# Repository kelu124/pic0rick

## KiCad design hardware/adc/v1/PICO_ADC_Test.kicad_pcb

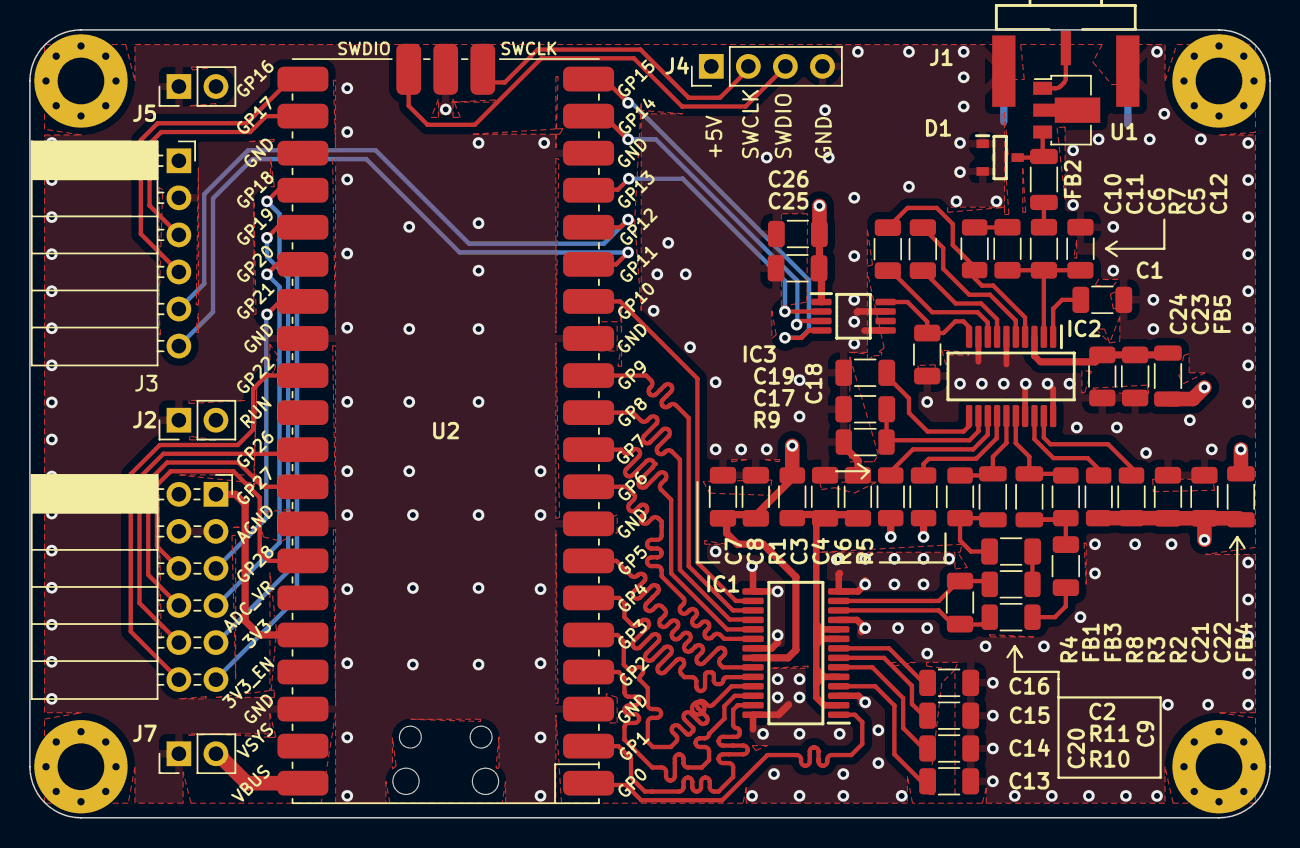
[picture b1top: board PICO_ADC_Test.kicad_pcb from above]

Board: 4 copper layers, 85.0 x 54.0 mm, 55 parts (0 on the bottom side), 63 nets.

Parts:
C1, C2, C4, C5, C8, C9, C10, C11, C13, C14, C15, C16, C17, C19, C22, C24, C26: 100nF; C_1206_3216Metric
C3, C7: 4.7uF; C_1206_3216Metric
C6: 18nF; C_1206_3216Metric
C12: 22pF; C_1206_3216Metric
C18, C21, C23: 1nF; C_1206_3216Metric
C20: 50pF; C_1206_3216Metric
C25: 10uF; C_1206_3216Metric
D1: BAV99-7-F; SOT95P240X120-3N
FB1, FB2, FB3, FB4, FB5: ILHB1206ER750V; L_1206_3216Metric
IC1: ADC10065CIMT_NOPB; SOP65P640X120-28N
IC2: AD8331ARQZ; SOP64P600X175-20N
IC3: MCP4812-E_MS; MCP4812-EMS
J1: AMPHENOL_132357-11
J2, J5, J7: 22-23-2021; PinHeader_1x02_P2.54mm_Vertical
J3: 61300611121; PinSocket_1x06_P2.54mm_Horizontal
J4: Conn_01x04; PinHeader_1x04_P2.54mm_Vertical
J6: 90122-0126; PinSocket_2x06_P2.54mm_Horizontal
R1, R10, R11: 18R; R_1206_3216Metric
R2, R3, R5, R6: 10K; R_1206_3216Metric
R4, R8: 100R; R_1206_3216Metric
R7: 280R; R_1206_3216Metric
R9: 12K; R_1206_3216Metric
U1: MD0100N8-G; SOT-89-3
U2: Pico; RPi_Pico_SMD

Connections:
5VLNA: C23.1, C24.1, FB5.2, IC2.3 (VPSL)
5VVGA: C21.1, C22.1, FB4.1, R2.1, R3.1, R5.1, R6.1
+3.3V: C7.1, C8.1, C25.1, C26.1, IC1.22 (VDDIO), IC3.1 (VDD), J3.1, J6.1, J6.2, R1.1, U2.36 (3V3)
+5V: FB4.2, FB5.1, J2.2, J4.1, J5.2, J7.2, U2.40 (VBUS)
ADC_CLK: IC1.1 (CLK), U2.1 (GPIO0)
CS: IC3.2 (~CS), U2.17 (GPIO13)
D0: IC1.27 (D0), U2.2 (GPIO1)
D1: IC1.26 (D1), U2.4 (GPIO2)
D2: IC1.25 (D2), U2.5 (GPIO3)
D3: IC1.24 (D3), U2.6 (GPIO4)
D4: IC1.23 (D4), U2.7 (GPIO5)
D5: IC1.20 (D5), U2.9 (GPIO6)
D6: IC1.19 (D6), U2.10 (GPIO7)
D7: IC1.18 (D7), U2.11 (GPIO8)
D8: IC1.17 (D8), U2.12 (GPIO9)
D9: IC1.16 (D9), U2.14 (GPIO10)
DAC_G: C18.1, IC2.10 (GAIN), IC3.8 (VOUTA)
GND: C1.1, C3.2, C4.2, C7.2, C8.2, C12.2, C13.2, C14.2, C15.2, C16.2, C17.2, C18.2, C19.2, C21.2, C22.2, C23.2, C24.2, C25.2, C26.2, D1.1, D1.2, IC1.3 (VSSA_1), IC1.11 (VSSA_2), IC1.14 (VSSA_3), IC1.15 (DF), IC1.21 (VSSIO), IC1.28 (STBY), IC2.6 (COML), IC2.9 (MODE), IC2.17 (COMM_1), IC2.20 (COMM_2), IC3.5 (~LDAC), IC3.7 (VSS), J1.2, J2.1, J3.2, J4.4, J5.1, J6.3, J6.4, J7.1, R9.2, U2.3 (GND), U2.8 (GND), U2.13 (GND), U2.18 (GND), U2.23 (GND), U2.28 (GND), U2.33 (AGND), U2.38 (GND), U2.42 (GND)
GPIO11: J3.6, U2.15 (GPIO11)
GPIO12: J3.5, U2.16 (GPIO12)
GPIO16: J3.4, U2.21 (GPIO16)
GPIO17: J3.3, U2.22 (GPIO17)
GPIO18: J6.11, U2.24 (GPIO18)
GPIO19: J6.9, U2.25 (GPIO19)
GPIO20: J6.7, U2.26 (GPIO20)
GPIO21: J6.5, U2.27 (GPIO21)
GPIO22: J6.12, U2.29 (GPIO22)
GPIO26: J6.10, U2.31 (GPIO26_ADC0)
GPIO27: J6.8, U2.32 (GPIO27_ADC1)
GPIO28: J6.6, U2.34 (GPIO28_ADC2)
MOSI: IC3.4 (SDI), U2.20 (GPIO15)
unnamed: C2.1, FB1.2, R4.2
unnamed: C5.1, FB2.2
unnamed: C6.2, R7.1
unnamed: C9.1, FB3.2, R8.2
unnamed: C3.1, C4.1, IC1.2 (VDDA_1), IC1.5 (IRS), IC1.9 (VDDA_2), IC1.10 (VDDA_3), R1.2
unnamed: C13.1, IC1.4 (VCOM)
unnamed: C20.2, IC1.13 (VIN+), R11.1
unnamed: C20.1, IC1.12 (VIN-), R10.1
unnamed: C14.1, IC1.6 (VREF)
unnamed: C16.1, IC1.8 (VREFB)
unnamed: C15.1, IC1.7 (VREFT)
unnamed: IC2.19 (ENBL), R2.2
unnamed: IC2.18 (ENBV), R3.2
unnamed: IC2.13 (HILO), R6.2
unnamed: C5.2, C6.1, C12.1, IC2.2 (INH)
unnamed: C1.2, IC2.1 (LMD)
unnamed: C10.1, IC2.4 (LON), R7.2
unnamed: C11.1, IC2.5 (LOP)
unnamed: C17.1, IC2.12 (RCLMP), R9.1
unnamed: C19.1, IC2.11 (VCM)
unnamed: C10.2, IC2.8 (VIN)
unnamed: C11.2, IC2.7 (VIP)
unnamed: IC2.14 (VPOS), R5.2
unnamed: J1.1, U1.1 (A)
unnamed: D1.3, FB2.1, U1.3 (B)
SCLK: IC3.3 (SCK), U2.19 (GPIO14)
SWCLK: J4.2, U2.41 (SWCLK)
SWDIO: J4.3, U2.43 (SWDIO)
TO_ADC_H: C2.2, R11.2
TO_ADC_L: C9.2, R10.2
VOH: FB1.1, IC2.15 (VOH), R4.1
VOL: FB3.1, IC2.16 (VOL), R8.1

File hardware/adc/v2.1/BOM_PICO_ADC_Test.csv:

"Reference","Value","Footprint","MPN","Manufacturer","Size","Qty"
"C1,C2,C4,C5,C8,C9,C10,C11,C13,C14,C15,C16,C17,C19,C22,C24,C26","100nF","Capacitor_SMD:C_1206_3216Metric","VJ1206Y104KXQCW1BC","","1206","17"
"C3,C7","4.7uF","Capacitor_SMD:C_1206_3216Metric","1206ZD475KAT4A","","1206","2"
"C6","18nF","Capacitor_SMD:C_1206_3216Metric","VJ1206Y183KXAAC","","1206","1"
"C12","22pF","Capacitor_SMD:C_1206_3216Metric","VJ1206A220JXQPW1BC","","1206","1"
"C18,C21,C23","1nF","Capacitor_SMD:C_1206_3216Metric","GRM31C5C3A102JWA3L","","1206","3"
"C20","50pF","Capacitor_SMD:C_1206_3216Metric","12062A500KAT2A","KYOCERA AVX","1206","1"
"C25","10uF","Capacitor_SMD:C_1206_3216Metric","KAF31GR71C106KU","KYOCERA AVX","1206","1"
"D1","BAV99-7-F","PICO_ADC_Test:SOT95P240X120-3N","BAV99-7-F","","SOT23","1"
"FB1,FB2,FB3,FB4,FB5","ILHB1206ER750V","Inductor_SMD:L_1206_3216Metric","BLM21BB750SN1D","","1206","5"
"IC1","ADC10065CIMT_NOPB","PICO_ADC_Test:SOP65P640X120-28N","ADC10065CIMT/NOPB","","","1"
"IC2","AD8331ARQZ","PICO_ADC_Test:SOP64P600X175-20N","584-AD8331ARQZ","","","1"
"IC3","MCP4812-E_MS","PICO_ADC_Test:MCP4812-EMS","579-MCP4812-E/MS","","","1"
"J1","AMPHENOL_132357-11","PICO_ADC_Test:AMPHENOL_132357-11","142-0701-801","","","1"
"J2,J5,J7","SSQ-101-02-L-Q-RA","Connector_PinHeader_2.54mm:PinHeader_1x02_P2.54mm_Vertical","SSQ-101-02-L-Q-RA","","","3"
"J3","61300611121","Connector_PinSocket_2.54mm:PinSocket_1x06_P2.54mm_Horizontal","613012243121","","","1"
"J4","61300411121","Connector_PinHeader_2.54mm:PinHeader_1x04_P2.54mm_Vertical","61300411121","","","1"
"J6","90122-0126","Connector_PinSocket_2.54mm:PinSocket_2x06_P2.54mm_Horizontal","613012243121","","","1"
"R1,R10,R11","18R","Resistor_SMD:R_1206_3216Metric","WSL1206R1800FEA","","1206","3"
"R2,R3,R5,R6","10K","Resistor_SMD:R_1206_3216Metric","1206W4F1002T5E","","1206","4"
"R4,R8","100R","Resistor_SMD:R_1206_3216Metric","560112132023","","1206","2"
"R7","280R","Resistor_SMD:R_1206_3216Metric","CR1206-FX-2800ELF","Bourns","1206","1"
"R9","12K","Resistor_SMD:R_1206_3216Metric","CR1206-FX-1202ELF","Bourns","1206","1"
"U1","MD0100N8-G","Package_TO_SOT_SMD:SOT-89-3","MD0100N8-G","","","1"
"U2","Pico","PICO_ADC_Test:RPi_Pico_SMD","Pico","","","1"

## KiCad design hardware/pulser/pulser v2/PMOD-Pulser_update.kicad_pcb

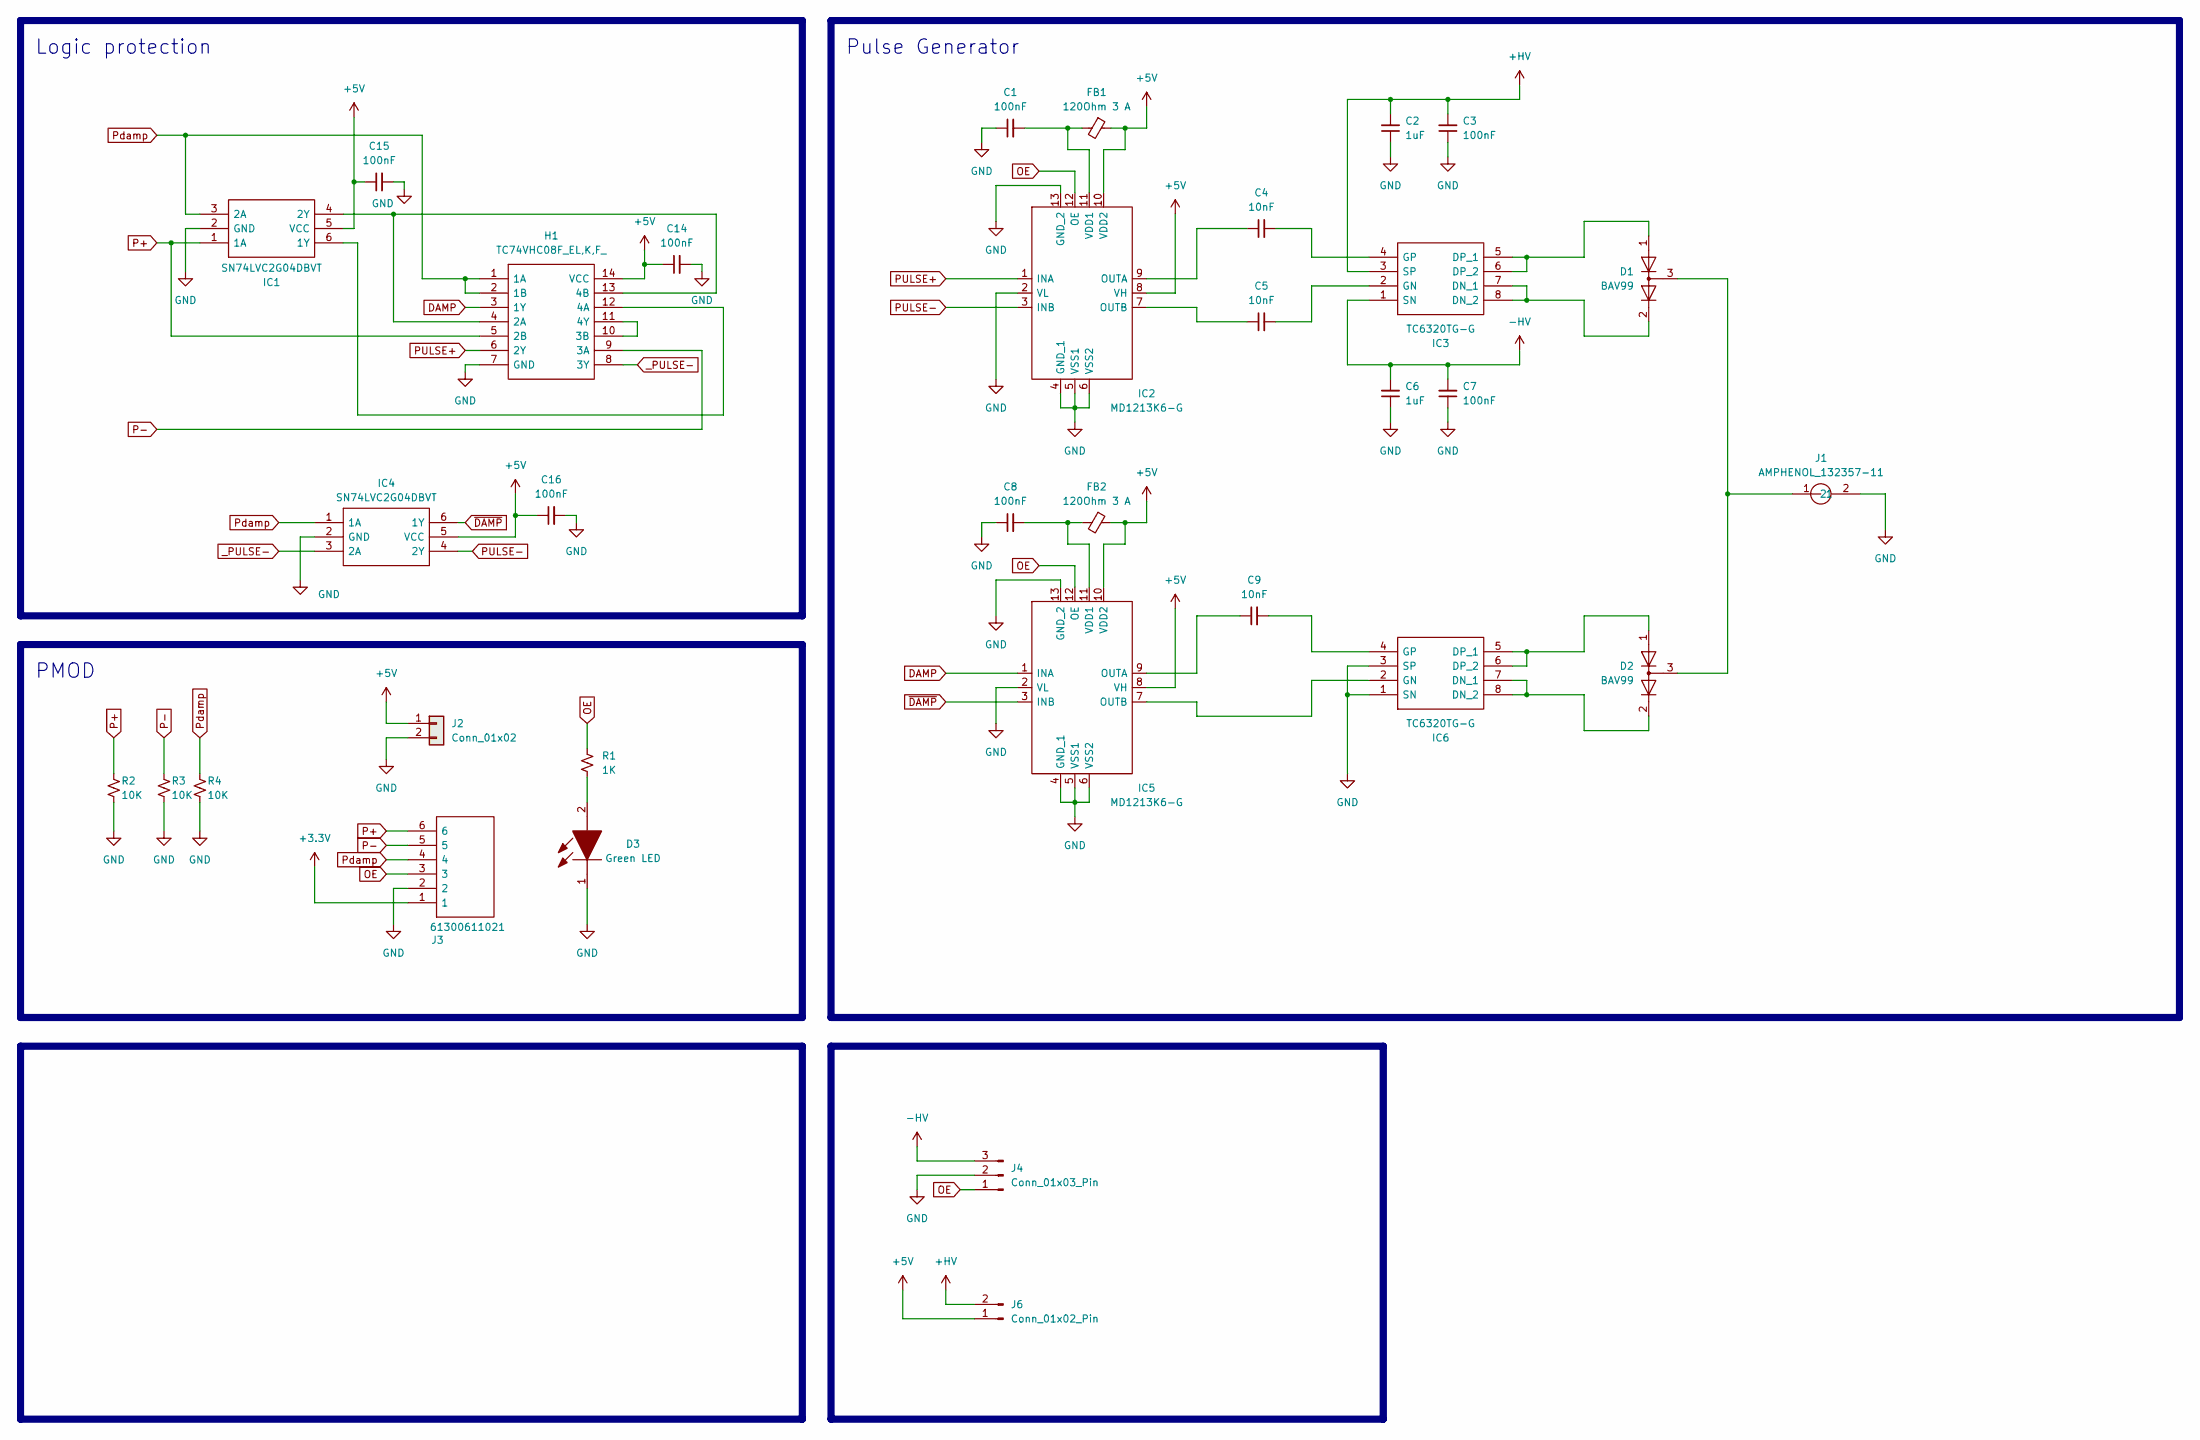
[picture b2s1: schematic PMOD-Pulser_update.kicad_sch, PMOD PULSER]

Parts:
C1, C3, C7, C8, C14, C15, C16: 100nF; C_1206_3216Metric
C2, C6: 1uF; C_1206_3216Metric
C4, C5, C9: 10nF; C_1206_3216Metric
D1, D2: BAV99; SOT-23; MPN BAV99
D3: Green LED; D_0805_2012Metric; MPN 150080GS75000; Mouser Part Number 710-150080GS75000
FB1, FB2: 120Ohm 3 A; L_1206_3216Metric; MPN 742792113
H1: TC74VHC08F_EL,K,F_; SOIC127P780X190-14N; Mouser Part Number 757-TC74VHC08FELKF
IC1, IC4: SN74LVC2G04DBVT; SN74LVC2G04DBV; Mouser Part Number 595-SN74LVC2G04DBVT
IC2, IC5: MD1213K6-G; MD1213; Mouser Part Number 689-MD1213K6-G
IC3, IC6: TC6320TG-G; SOIC127P600X175-8N; Mouser Part Number 689-TC6320TG-G
J1: AMPHENOL_132357-11; Mouser Part Number 530-142-0701-801
J2: Conn_01x02; PinHeader_2x01_P2.54mm_Horizontal
J3: 61300611021; PinHeader_1x06_P2.54mm_Horizontal; MPN 61300611021; Mouser Part Number 710-61300611021
J4: Conn_01x03_Pin; PinHeader_1x03_P2.54mm_Vertical
J6: Conn_01x02_Pin; PinHeader_1x02_P2.54mm_Vertical
R1: 1K; R_1206_3216Metric
R2, R3, R4: 10K; R_1206_3216Metric

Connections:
+3.3V: J3.1
+5V: C14.1, C15.1, C16.1, FB1.1, FB2.1, H1.14 (VCC), IC1.5 (VCC), IC2.8 (VH), IC2.10 (VDD2), IC4.5 (VCC), IC5.8 (VH), IC5.10 (VDD2), J2.1, J6.1
+HV: C2.2, C3.2, IC3.3 (SP), J6.2
-HV: C6.2, C7.2, IC3.1 (SN), J4.3
DAMP: H1.3 (1Y), IC5.1 (INA)
GND: C1.1, C2.1, C3.1, C6.1, C7.1, C8.1, C14.2, C15.2, C16.2, D3.1, H1.7 (GND), IC1.2 (GND), IC2.2 (VL), IC2.4 (GND_1), IC2.5 (VSS1), IC2.6 (VSS2), IC2.13 (GND_2), IC4.2 (GND), IC5.2 (VL), IC5.4 (GND_1), IC5.5 (VSS1), IC5.6 (VSS2), IC5.13 (GND_2), IC6.1 (SN), IC6.3 (SP), J1.2, J2.2, J3.2, J4.2, R2.2, R3.2, R4.2
unnamed: D1.2 (A), IC3.7 (DN_1), IC3.8 (DN_2)
unnamed: D1.3 (K), D2.3 (K), J1.1
unnamed: D2.2 (A), IC6.7 (DN_1), IC6.8 (DN_2)
unnamed: D3.2, R1.2
unnamed: H1.4 (2A), H1.13 (4B), IC1.4 (2Y)
unnamed: H1.10 (3B), H1.11 (4Y)
unnamed: H1.12 (4A), IC1.6 (1Y)
unnamed: C4.1, IC2.9 (OUTA)
unnamed: C5.1, IC2.7 (OUTB)
unnamed: C1.2, FB1.2, IC2.11 (VDD1)
unnamed: D1.1 (K), IC3.5 (DP_1), IC3.6 (DP_2)
unnamed: C5.2, IC3.2 (GN)
unnamed: C4.2, IC3.4 (GP)
unnamed: C9.1, IC5.9 (OUTA)
unnamed: IC5.7 (OUTB), IC6.2 (GN)
unnamed: C8.2, FB2.2, IC5.11 (VDD1)
unnamed: D2.1 (K), IC6.5 (DP_1), IC6.6 (DP_2)
unnamed: C9.2, IC6.4 (GP)
OE: IC2.12 (OE), IC5.12 (OE), J3.3, J4.1, R1.1
P+: H1.5 (2B), IC1.1 (1A), J3.6, R2.1
P-: H1.9 (3A), J3.5, R3.1
PULSE+: H1.6 (2Y), IC2.1 (INA)
PULSE-: IC2.3 (INB), IC4.4 (2Y)
Pdamp: H1.1 (1A), H1.2 (1B), IC1.3 (2A), IC4.1 (1A), J3.4, R4.1
_PULSE-: H1.8 (3Y), IC4.3 (2A)
~DAMP: IC4.6 (1Y), IC5.3 (INB)

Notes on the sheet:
PMOD
Logic protection
Pulse Generator

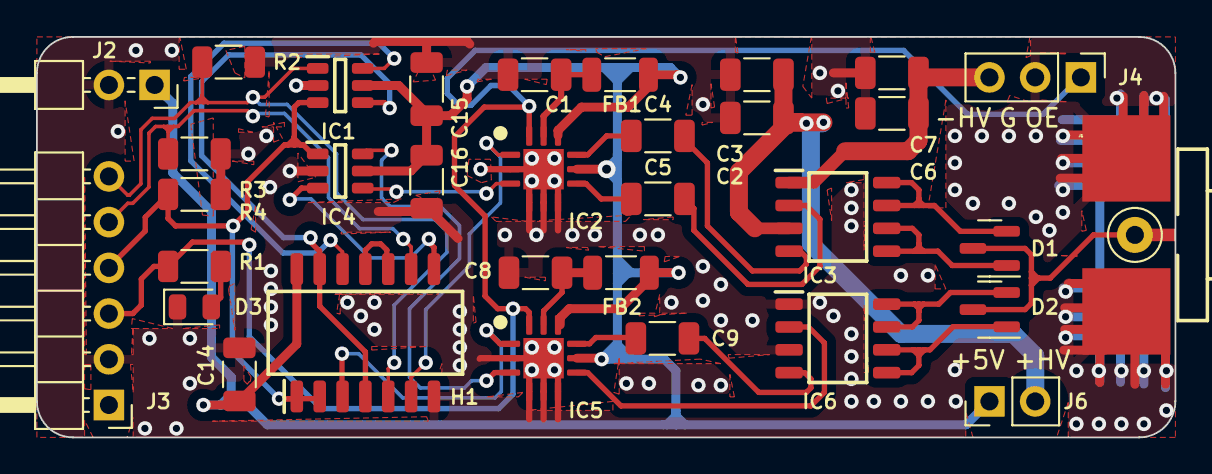
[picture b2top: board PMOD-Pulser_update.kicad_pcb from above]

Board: 2 copper layers, 63.2 x 22.2 mm, 33 parts (0 on the bottom side), 31 nets.
